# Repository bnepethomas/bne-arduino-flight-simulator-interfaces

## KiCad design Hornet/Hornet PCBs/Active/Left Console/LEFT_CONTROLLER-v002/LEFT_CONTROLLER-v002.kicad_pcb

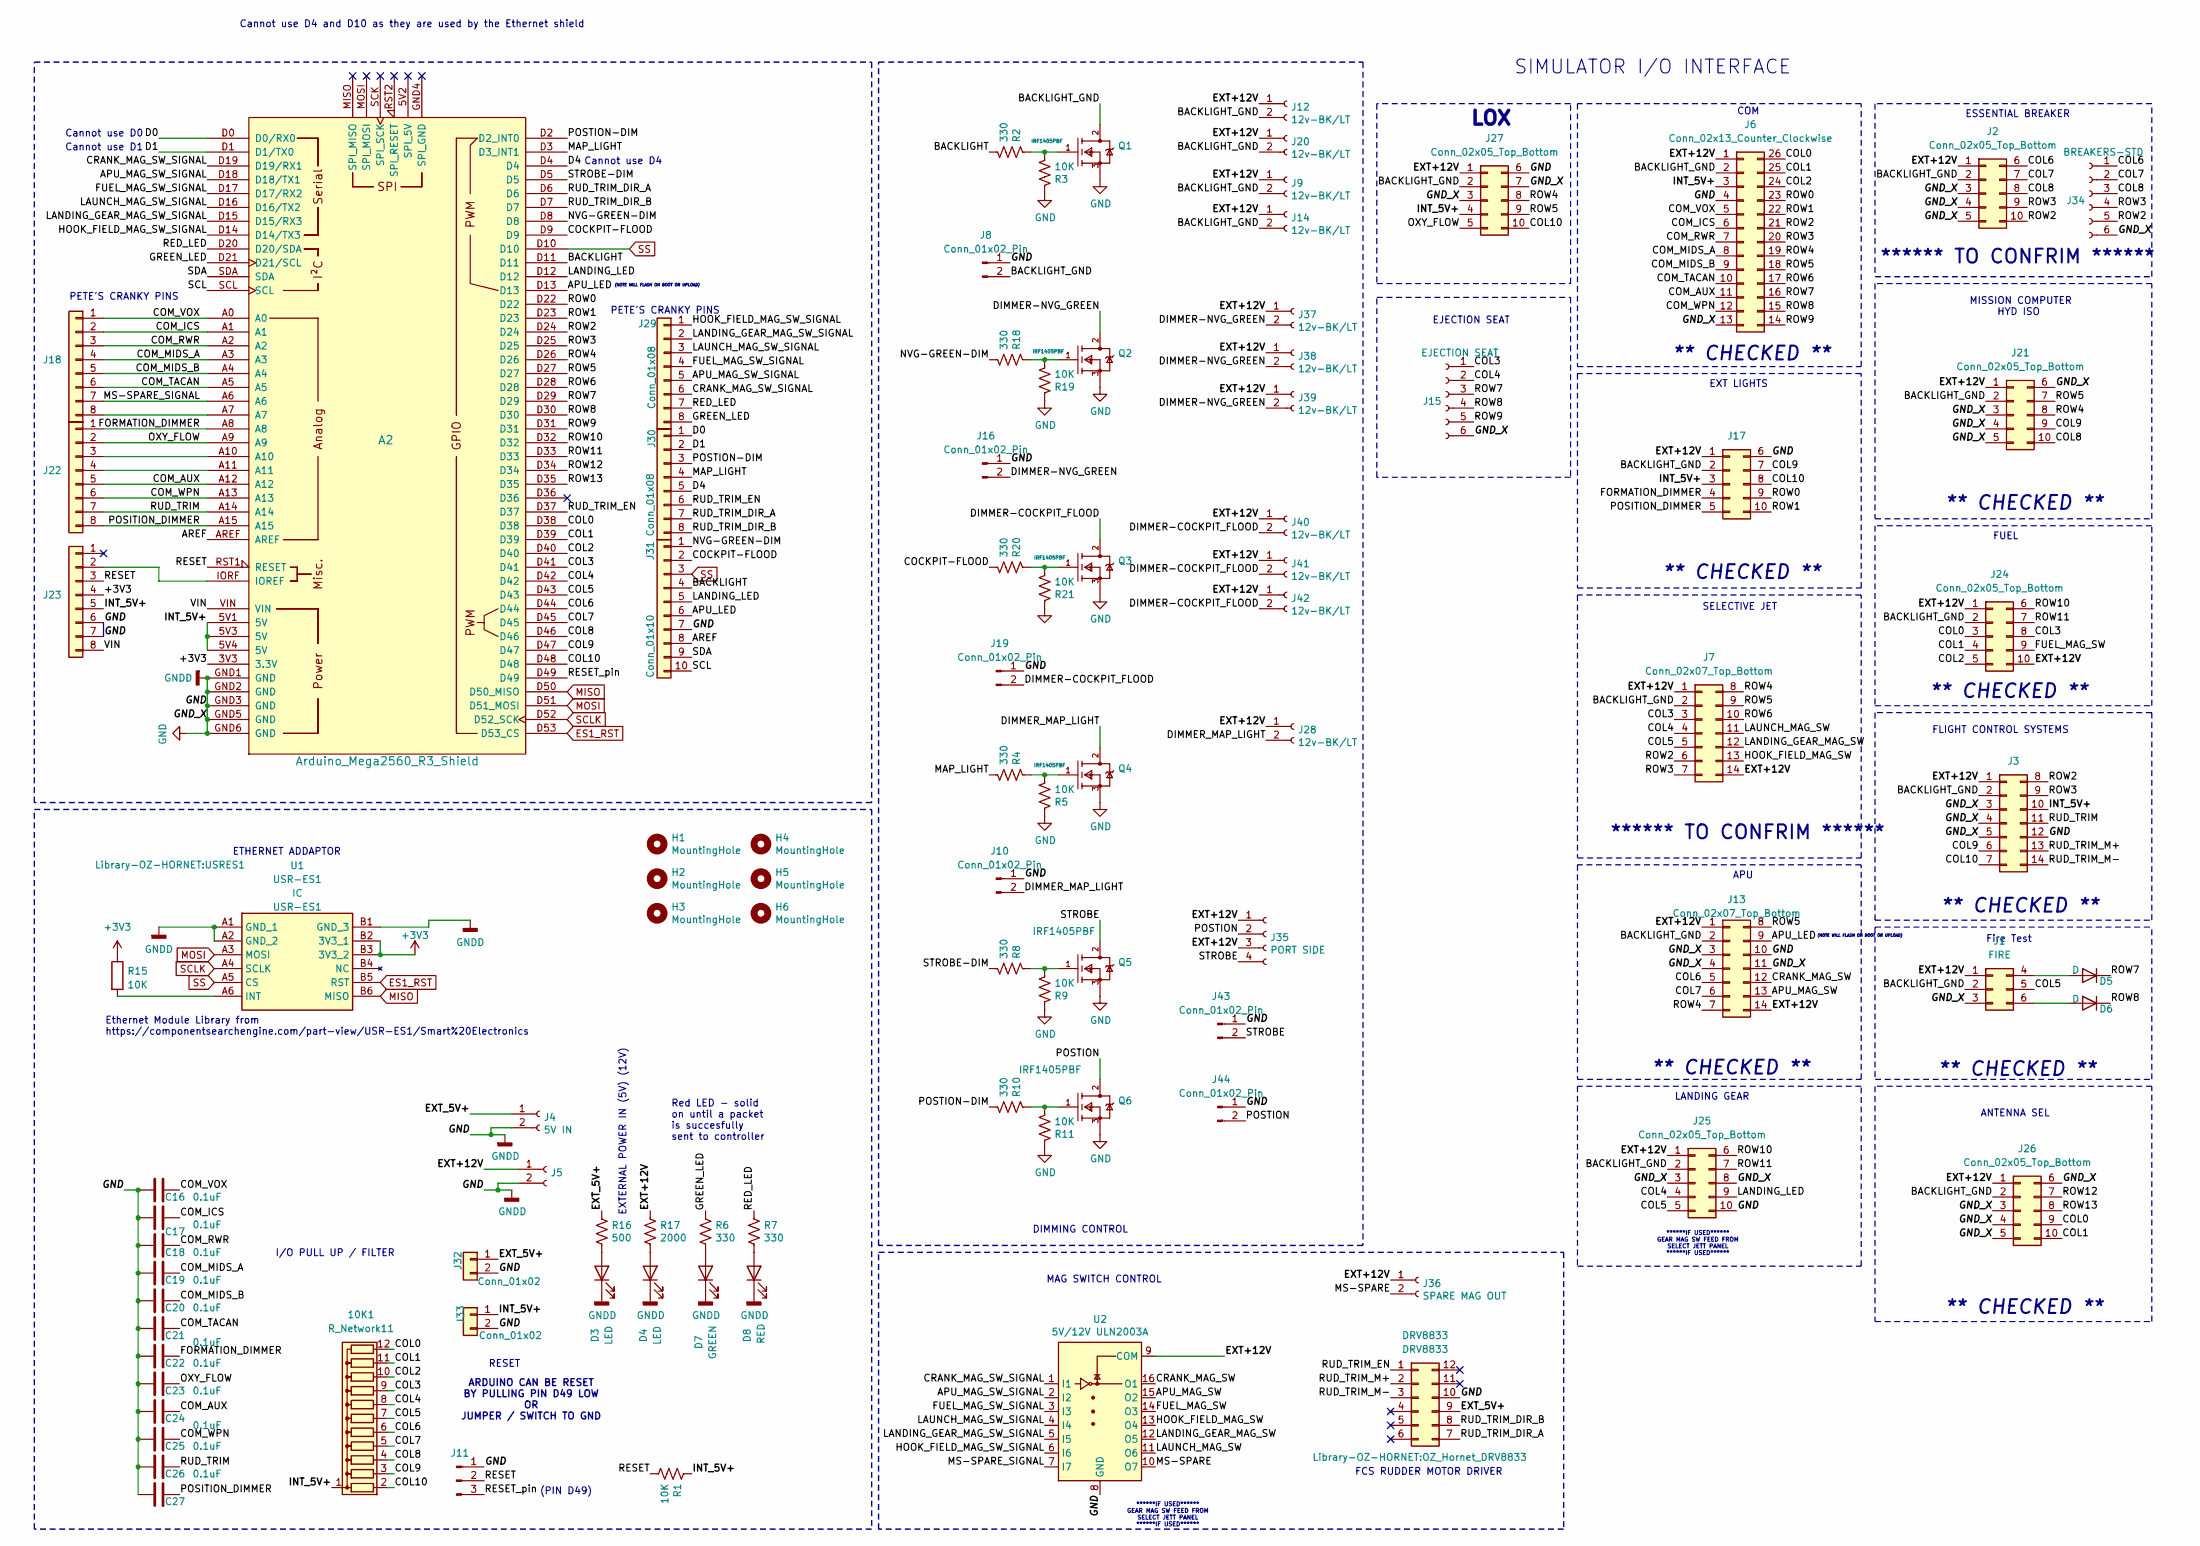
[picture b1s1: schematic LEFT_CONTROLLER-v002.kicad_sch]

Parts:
10K1: R_Network11; R_Array_SIP12
A2: Arduino_Mega2560_R3_Shield
C16, C17, C18, C19, C20, C21, C22, C23, C24, C25, C26, C27: 0.1uF; C_Disc_D4.3mm_W1.9mm_P5.00mm
D3, D4: LED; LED_D3.0mm
D5, D6: D; D_A-405_P7.62mm_Horizontal-SIGNAL
D7: GREEN; LED_D3.0mm
D8: RED; LED_D3.0mm
DRV8833: DRV8833; OZ_Hornet_DRV8833
H1, H2, H3, H4, H5, H6: MountingHole; MountingHole_3.2mm_M3
J1: FIRE; IDC-Header_2x03_P2.54mm_Vertical
J2, J17, J21, J24, J25, J26, J27: Conn_02x05_Top_Bottom; IDC-Header_2x05_P2.54mm_Vertical
J3, J7, J13: Conn_02x07_Top_Bottom; IDC-Header_2x07_P2.54mm_Vertical
J4: 5V IN; BarrelJack_Horizontal
J5: STEPPER IN 12-20VDC; BarrelJack_Horizontal
J6: Conn_02x13_Counter_Clockwise; IDC-Header_2x13_P2.54mm_Vertical
J8, J10, J16, J19, J43, J44: Conn_01x02_Pin; PinHeader_1x02_P2.54mm_Vertical
J9, J12, J14, J20, J28, J37, J38, J39, J40, J41, J42: 12v-BK/LT; Molex_KK-254_AE-6410-02A_1x02_P2.54mm_Vertical
J11: Conn_01x03_Pin; PinHeader_1x03_P2.54mm_Vertical
J15: EJECTION SEAT; Molex_KK-254_AE-6410-06A_1x06_P2.54mm_Vertical
J18, J22, J23, J29, J30: Conn_01x08; PinHeader_1x08_P2.54mm_Vertical
J31: Conn_01x10; PinHeader_1x10_P2.54mm_Vertical
J32, J33: Conn_01x02; PinHeader_1x02_P2.54mm_Vertical
J34: BREAKERS-STD; Molex_KK-254_AE-6410-06A_1x06_P2.54mm_Vertical
J35: PORT SIDE; Molex_KK-254_AE-6410-04A_1x04_P2.54mm_Vertical
J36: SPARE MAG OUT; Molex_KK-254_AE-6410-02A_1x02_P2.54mm_Vertical
Q1, Q2, Q3, Q4, Q5, Q6: IRF1405PBF; TO-220-3_Vertical; mouser part number 942-IRF1405PBF; digikey description MOSFET N-CH 55V 169A TO-220AB
R1, R3, R5, R9, R11, R15, R19, R21: 10K; R_Axial_DIN0204_L3.6mm_D1.6mm_P7.62mm_Horizontal
R2, R4, R6, R7, R8, R10, R18, R20: 330; R_Axial_DIN0204_L3.6mm_D1.6mm_P7.62mm_Horizontal
R16: 500; R_Axial_DIN0204_L3.6mm_D1.6mm_P7.62mm_Horizontal
R17: 2000; R_Axial_DIN0204_L3.6mm_D1.6mm_P7.62mm_Horizontal
U1: USR-ES1; USRES1; Manufacturer_Part_Number USR-ES1
U2: 5V/12V ULN2003A; DIP-16_W7.62mm

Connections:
+3V3: A2.3V3 (3.3V), J23.4, R15.1, U1.B2 (3V3_1), U1.B3 (3V3_2)
/APU_LED: A2.D13, J13.9, J31.6
/APU_MAG_SW: J13.13, U2.15 (O2)
/APU_MAG_SW_SIGNAL: A2.D18 (D18/TX1), J29.5, U2.2 (I2)
/AREF: A2.AREF, J31.8
/BACKLIGHT: A2.D11, J31.4, R2.2
/BACKLIGHT_GND: J1.2, J2.2, J3.2, J6.2, J7.2, J8.2, J9.2, J12.2, J13.2, J14.2, J17.2, J20.2, J21.2, J24.2, J25.2, J26.2, J27.2, Q1.2 (D)
/COCKPIT-FLOOD: A2.D9, J31.2, R20.2
/COL0: 10K1.12 (R11), A2.D38, J6.26, J24.3, J26.9
/COL1: 10K1.11 (R10), A2.D39, J6.25, J24.4, J26.10
/COL2: 10K1.10 (R9), A2.D40, J6.24, J24.5
/COL3: 10K1.9 (R8), A2.D41, J7.3, J15.1, J24.8
/COL4: 10K1.8 (R7), A2.D42, J7.4, J15.2, J25.4
/COL5: 10K1.7 (R6), A2.D43, J1.5, J7.5, J25.5
/COL6: 10K1.6 (R5), A2.D44, J2.6, J13.5, J34.1
/COL7: 10K1.5 (R4), A2.D45, J2.7, J13.6, J34.2
/COL8: 10K1.4 (R3), A2.D46, J2.8, J21.10, J34.3
/COL9: 10K1.3 (R2), A2.D47, J3.6, J17.7, J21.9
/COL10: 10K1.2 (R1), A2.D48, J3.7, J17.8, J27.10
/COM_AUX: A2.A12, C24.1, J6.11, J22.5
/COM_ICS: A2.A1, C17.1, J6.6, J18.2
/COM_MIDS_A: A2.A3, C19.1, J6.8, J18.4
/COM_MIDS_B: A2.A4, C20.1, J6.9, J18.5
/COM_RWR: A2.A2, C18.1, J6.7, J18.3
/COM_TACAN: A2.A5, C21.1, J6.10, J18.6
/COM_VOX: A2.A0, C16.1, J6.5, J18.1
/COM_WPN: A2.A13, C25.1, J6.12, J22.6
/CRANK_MAG_SW: J13.12, U2.16 (O1)
/CRANK_MAG_SW_SIGNAL: A2.D19 (D19/RX1), J29.6, U2.1 (I1)
/D0: A2.D0 (D0/RX0), J30.1
/D1: A2.D1 (D1/TX0), J30.2
/D4: A2.D4, J30.5
/DIMMER-COCKPIT_FLOOD: J19.2, J40.2, J41.2, J42.2, Q3.2 (D)
/DIMMER-NVG_GREEN: J16.2, J37.2, J38.2, J39.2, Q2.2 (D)
/DIMMER_MAP_LIGHT: J10.2, J28.2, Q4.2 (D)
/EXT+12V: J1.1, J2.1, J3.1, J5.1, J6.1, J7.1, J7.14, J9.1, J12.1, J13.1, J13.14, J14.1, J17.1, J20.1, J21.1, J24.1, J24.10, J25.1, J26.1, J27.1, J28.1, J35.1, J35.3, J36.1, J37.1, J38.1, J39.1, J40.1, J41.1, J42.1, R17.1, U2.9 (COM)
/EXT_5V+: DRV8833.9, J4.1, J32.1, R16.1
/FORMATION_DIMMER: A2.A8, C22.1, J17.4, J22.1
/FUEL_MAG_SW: J24.9, U2.14 (O3)
/FUEL_MAG_SW_SIGNAL: A2.D17 (D17/RX2), J29.4, U2.3 (I3)
/GREEN_LED: A2.D21 (D21/SCL), J29.8, R6.1
/HOOK_FIELD_MAG_SW: J7.13, U2.13 (O4)
/HOOK_FIELD_MAG_SW_SIGNAL: A2.D14 (D14/TX3), J29.1, U2.6 (I6)
/INT_5V+: 10K1.1 (common), A2.5V1 (5V), A2.5V3 (5V), A2.5V4 (5V), J3.10, J6.3, J17.3, J23.5, J27.4, J33.1, R1.1
/LANDING_GEAR_MAG_SW: J7.12, U2.12 (O5)
/LANDING_GEAR_MAG_SW_SIGNAL: A2.D15 (D15/RX3), J29.2, U2.5 (I5)
/LANDING_LED: A2.D12, J25.9, J31.5
/LAUNCH_MAG_SW: J7.11, U2.11 (O6)
/LAUNCH_MAG_SW_SIGNAL: A2.D16 (D16/TX2), J29.3, U2.4 (I4)
/MAP_LIGHT: A2.D3 (D3_INT1), J30.4, R4.2
/MS-SPARE: J36.2, U2.10 (O7)
/MS-SPARE_SIGNAL: A2.A6, J18.7, U2.7 (I7)
/NVG-GREEN-DIM: A2.D8, J31.1, R18.2
/OXY_FLOW: A2.A9, C23.1, J22.2, J27.5
/POSITION_DIMMER: A2.A15, C27.1, J17.5, J22.8
/POSTION: J35.2, J44.2, Q6.2 (D)
/POSTION-DIM: A2.D2 (D2_INT0), J30.3, R10.2
/RED_LED: A2.D20 (D20/SDA), J29.7, R7.1
/RESET: A2.RST1 (RESET), J11.2, J23.3, R1.2
/RESET_pin: A2.D49, J11.3
/ROW0: A2.D22, J6.23, J17.9
/ROW1: A2.D23, J6.22, J17.10
/ROW2: A2.D24, J2.10, J3.8, J6.21, J7.6, J34.5
/ROW3: A2.D25, J2.9, J3.9, J6.20, J7.7, J34.4
/ROW4: A2.D26, J6.19, J7.8, J13.7, J21.8, J27.8
/ROW5: A2.D27, J6.18, J7.9, J13.8, J21.7, J27.9
/ROW6: A2.D28, J6.17, J7.10
/ROW7: A2.D29, D5.1 (K), J6.16, J15.3
/ROW8: A2.D30, D6.1 (K), J6.15, J15.4
/ROW9: A2.D31, J6.14, J15.5
/ROW10: A2.D32, J24.6, J25.6
/ROW11: A2.D33, J24.7, J25.7
/ROW12: A2.D34, J26.7
/ROW13: A2.D35, J26.8
/RUD_TRIM: A2.A14, C26.1, J3.11, J22.7
/RUD_TRIM_DIR_A: A2.D6, DRV8833.7, J30.7
/RUD_TRIM_DIR_B: A2.D7, DRV8833.8, J30.8
/RUD_TRIM_EN: A2.D37, DRV8833.1, J30.6
/RUD_TRIM_M+: DRV8833.2, J3.13
/RUD_TRIM_M-: DRV8833.3, J3.14
/SCL: A2.SCL, J31.10
/SDA: A2.SDA, J31.9
/STROBE: J35.4, J43.2, Q5.2 (D)
/STROBE-DIM: A2.D5, R8.2
/VIN: A2.VIN, J23.8
ES1_RST: A2.D53 (D53_CS), U1.B5 (RST)
GND: A2.GND1 (GND), A2.GND2 (GND), A2.GND3 (GND), A2.GND5 (GND), A2.GND6 (GND), C16.2, C17.2, C18.2, C19.2, C20.2, C21.2, C22.2, C23.2, C24.2, C25.2, C26.2, C27.2, D3.1 (K), D4.1 (K), D7.1 (K), D8.1 (K), DRV8833.10, J1.3, J2.3, J2.4, J2.5, J3.3, J3.4, J3.5, J3.12, J4.2, J5.2, J6.4, J6.13, J8.1, J10.1, J11.1, J13.3, J13.4, J13.10, J13.11, J15.6, J16.1, J17.6, J19.1, J21.3, J21.4, J21.5, J21.6, J23.6, J23.7, J25.3, J25.8, J25.10, J26.3, J26.4, J26.5, J26.6, J27.3, J27.6, J27.7, J31.7, J32.2, J33.2, J34.6, J43.1, J44.1, Q1.3 (S), Q2.3 (S), Q3.3 (S), Q4.3 (S), Q5.3 (S), Q6.3 (S), R3.1, R5.1, R9.1, R11.1, R19.1, R21.1, U1.A1 (GND_1), U1.A2 (GND_2), U1.B1 (GND_3), U2.8 (GND)
MISO: A2.D50 (D50_MISO), U1.B6 (MISO)
MOSI: A2.D51 (D51_MOSI), U1.A3 (MOSI)
unnamed: A2.IORF (IOREF), J23.2
unnamed: D3.2 (A), R16.2
unnamed: D4.2 (A), R17.2
unnamed: D5.2 (A), J1.4
unnamed: D6.2 (A), J1.6
unnamed: D7.2 (A), R6.2
unnamed: D8.2 (A), R7.2
unnamed: A2.A7, J18.8
unnamed: A2.A10, J22.3
unnamed: A2.A11, J22.4
unnamed: Q1.1 (G), R2.1, R3.2
unnamed: Q2.1 (G), R18.1, R19.2
unnamed: Q3.1 (G), R20.1, R21.2
unnamed: Q4.1 (G), R4.1, R5.2
unnamed: Q5.1 (G), R8.1, R9.2
unnamed: Q6.1 (G), R10.1, R11.2
unnamed: R15.2, U1.A6 (INT)
SCLK: A2.D52 (D52_SCK), U1.A4 (SCLK)
SS: A2.D10, J31.3, U1.A5 (CS)

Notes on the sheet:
ANTENNA SEL
** CHECKED **
(NOTE WILL FLASH ON BOOT OR UPLOAD)
EJECTION SEAT
EXT LIGHTS
COM
Fire Test
FLIGHT CONTROL SYSTEMS
PETE'S CRANKY PINS
******IF USED****** GEAR MAG SW FEED FROM SELECT JETT PANEL ******IF USED******
SIMULATOR I/O INTERFACE
EXTERNAL POWER IN (5V) (12V)
RESET
****** TO CONFRIM ******
FUEL
APU
I/O PULL UP / FILTER
Cannot use D1
Cannot use D0
ESSENTIAL BREAKER
FCS RUDDER MOTOR DRIVER
LOX
HYD ISO
DIMMING CONTROL
ARDUINO CAN BE RESET BY PULLING PIN D49 LOW OR JUMPER / SWITCH TO GND
ETHERNET ADDAPTOR
SELECTIVE JET
Cannot use D4
Ethernet Module Library from https://componentsearchengine.com/part-view/USR-ES1/Smart%20Electronics
Red LED - solid on until a packet is succesfully sent to controller
(PIN D49)
MAG SWITCH CONTROL
Cannot use D4 and D10 as they are used by the Ethernet shield
LANDING GEAR
MISSION COMPUTER

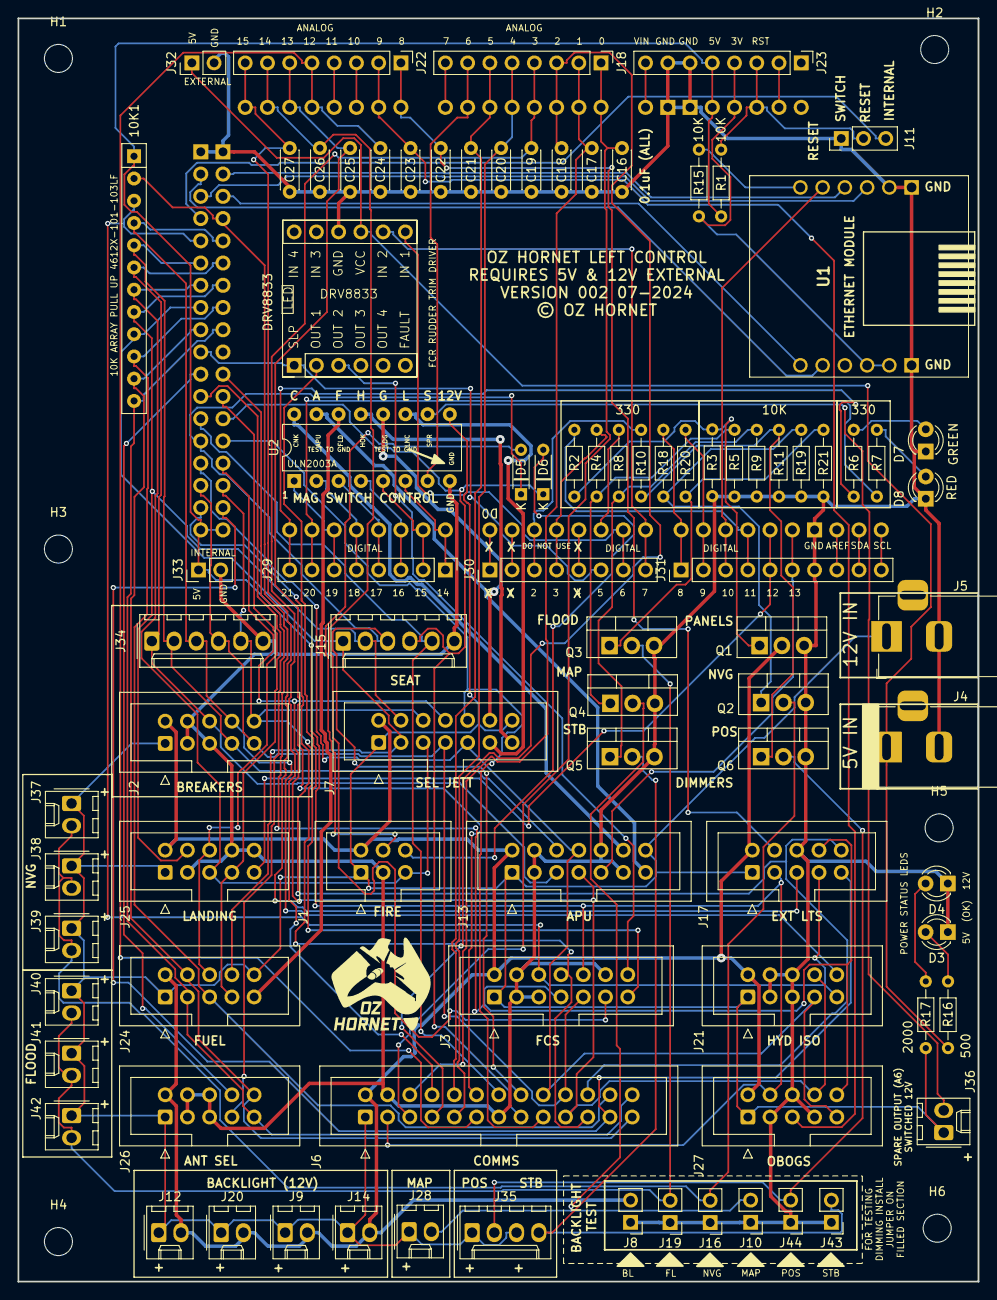
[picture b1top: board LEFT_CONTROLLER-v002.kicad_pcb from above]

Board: 2 copper layers, 109.7 x 144.3 mm, 97 parts (0 on the bottom side), 108 nets.

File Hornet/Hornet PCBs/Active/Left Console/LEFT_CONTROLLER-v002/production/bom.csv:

Designator,Footprint,Quantity,Value,LCSC Part #
10K1,R_Array_SIP12,1,R_Network11,
A2,Arduino_Mega2560_R3_Shield,1,Arduino_Mega2560_R3_Shield,
"C16, C17, C18, C19, C20, C21, C22, C23, C24, C25, C26, C27",C_Disc_D4.3mm_W1.9mm_P5.00mm,12,0.1uF,
"D3, D4",LED_D3.0mm,2,LED,
"D5, D6",D_A-405_P7.62mm_Horizontal-SIGNAL,2,D,
D7,LED_D3.0mm,1,GREEN,
D8,LED_D3.0mm,1,RED,
DRV8833,OZ_Hornet_DRV8833,1,DRV8833,
"H1, H2, H3, H4, H5, H6",MountingHole_3.2mm_M3,6,MountingHole,
J1,IDC-Header_2x03_P2.54mm_Vertical,1,FIRE,
"J10, J16, J19, J43, J44, J8",PinHeader_1x02_P2.54mm_Vertical,6,Conn_01x02_Pin,
J11,PinHeader_1x03_P2.54mm_Vertical,1,Conn_01x03_Pin,
"J12, J14, J20, J28, J37, J38, J39, J40, J41, J42, J9",Molex_KK-254_AE-6410-02A_1x02_P2.54mm_Vertical,11,12v-BK/LT,
"J13, J3, J7",IDC-Header_2x07_P2.54mm_Vertical,3,Conn_02x07_Top_Bottom,
J15,Molex_KK-254_AE-6410-06A_1x06_P2.54mm_Vertical,1,EJECTION SEAT,
"J17, J2, J21, J24, J25, J26, J27",IDC-Header_2x05_P2.54mm_Vertical,7,Conn_02x05_Top_Bottom,
"J18, J22, J23, J29, J30",PinHeader_1x08_P2.54mm_Vertical,5,Conn_01x08,
J31,PinHeader_1x10_P2.54mm_Vertical,1,Conn_01x10,
"J32, J33",PinHeader_1x02_P2.54mm_Vertical,2,Conn_01x02,
J34,Molex_KK-254_AE-6410-06A_1x06_P2.54mm_Vertical,1,BREAKERS-STD,
J35,Molex_KK-254_AE-6410-04A_1x04_P2.54mm_Vertical,1,PORT SIDE,
J36,Molex_KK-254_AE-6410-02A_1x02_P2.54mm_Vertical,1,SPARE MAG OUT,
J4,BarrelJack_Horizontal,1,5V IN,
J5,BarrelJack_Horizontal,1,STEPPER IN 12-20VDC,
J6,IDC-Header_2x13_P2.54mm_Vertical,1,Conn_02x13_Counter_Clockwise,
"Q1, Q2, Q3, Q4, Q5, Q6",TO-220-3_Vertical,6,IRF1405PBF,
"R1, R11, R15, R19, R21, R3, R5, R9",R_Axial_DIN0204_L3.6mm_D1.6mm_P7.62mm_Horizontal,8,10K,
"R10, R18, R2, R20, R4, R6, R7, R8",R_Axial_DIN0204_L3.6mm_D1.6mm_P7.62mm_Horizontal,8,330,
R16,R_Axial_DIN0204_L3.6mm_D1.6mm_P7.62mm_Horizontal,1,500,
R17,R_Axial_DIN0204_L3.6mm_D1.6mm_P7.62mm_Horizontal,1,2000,
U1,USRES1,1,USR-ES1,
U2,DIP-16_W7.62mm,1,5V/12V ULN2003A,

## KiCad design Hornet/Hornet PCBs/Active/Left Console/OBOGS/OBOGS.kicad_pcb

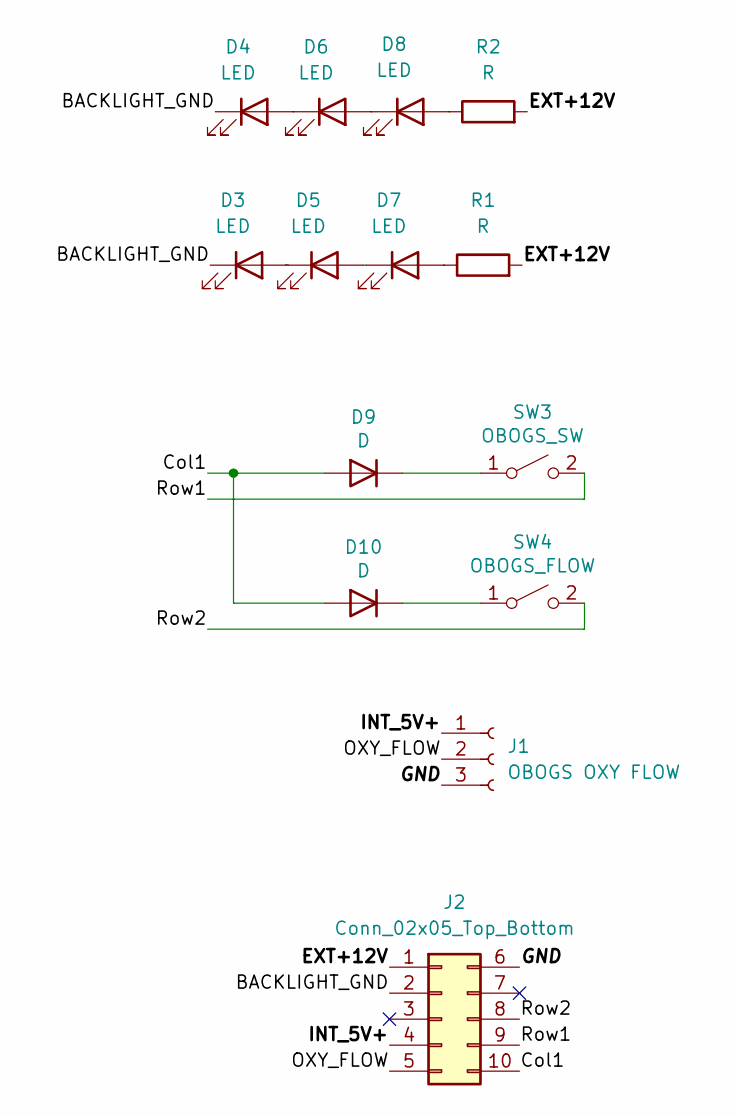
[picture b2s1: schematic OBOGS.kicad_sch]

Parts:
D3, D4, D5, D6, D7, D8: LED; LED_D3.0mm_FlatTop
D9, D10: D; D_A-405_P7.62mm_Horizontal-SIGNAL
J1: OBOGS OXY FLOW; JST_XH_B3B-XH-A_1x03_P2.50mm_Vertical
J2: Conn_02x05_Top_Bottom; IDC-Header_2x05_P2.54mm_Vertical
R1, R2: R; R_Axial_DIN0204_L3.6mm_D1.6mm_P7.62mm_Horizontal
SW3: OBOGS_SW; JST_XH_B2B-XH-A_1x02_P2.50mm_Vertical
SW4: OBOGS_FLOW; JST_XH_B2B-XH-A_1x02_P2.50mm_Vertical

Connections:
/BACKLIGHT_GND: D3.1 (K), D4.1 (K), J2.2
/Col1: D9.2 (A), D10.2 (A), J2.10
/EXT+12V: J2.1, R1.2, R2.2
/GND: J1.3, J2.6
/INT_5V+: J1.1, J2.4
/OXY_FLOW: J1.2, J2.5
/Row1: J2.9, SW3.2 (B)
/Row2: J2.8, SW4.2 (B)
unnamed: D3.2 (A), D5.1 (K)
unnamed: D4.2 (A), D6.1 (K)
unnamed: D5.2 (A), D7.1 (K)
unnamed: D6.2 (A), D8.1 (K)
unnamed: D7.2 (A), R1.1
unnamed: D8.2 (A), R2.1
unnamed: D9.1 (K), SW3.1 (A)
unnamed: D10.1 (K), SW4.1 (A)

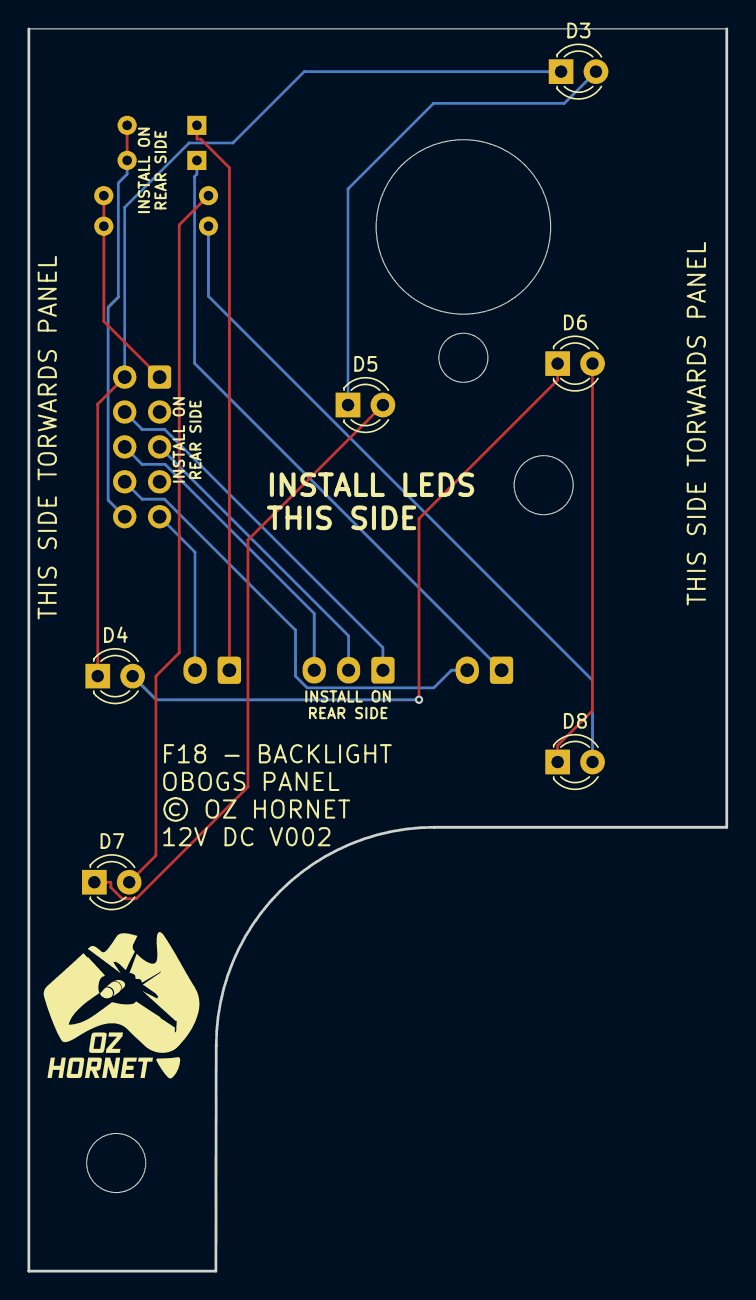
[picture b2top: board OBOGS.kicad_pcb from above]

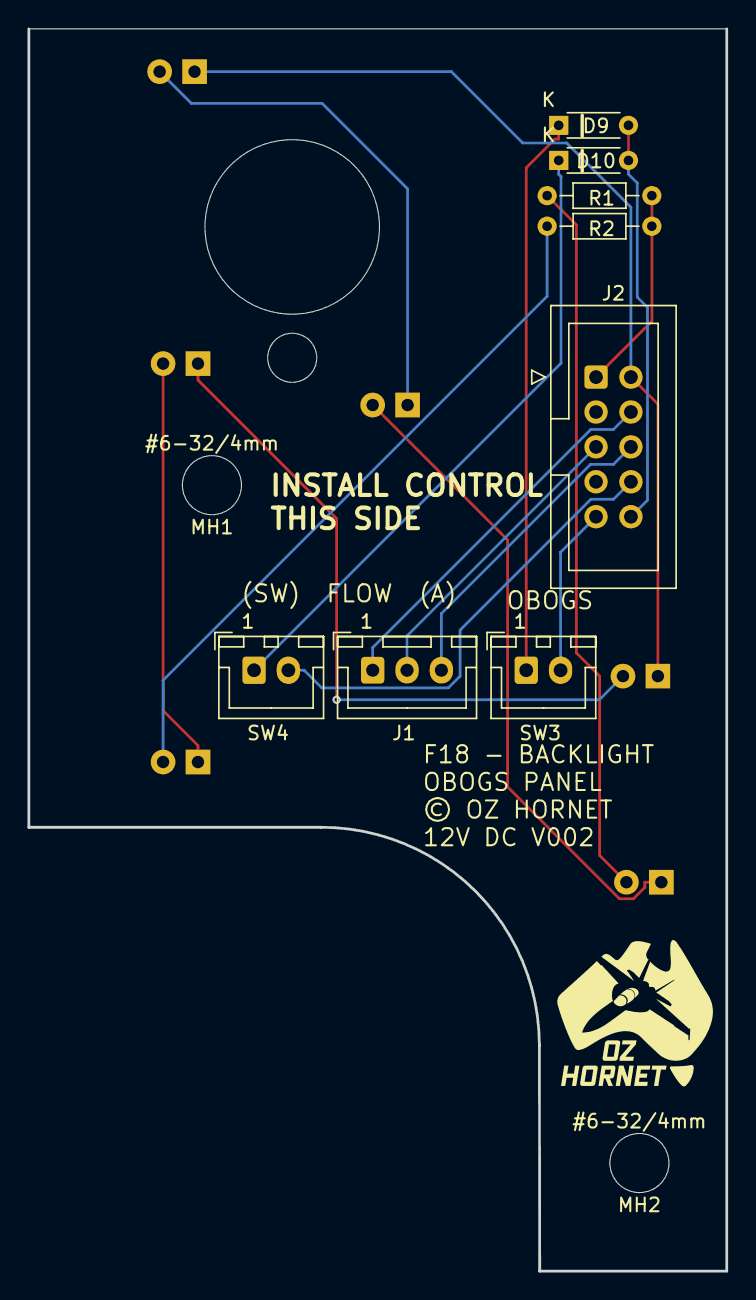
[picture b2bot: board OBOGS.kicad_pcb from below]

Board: 2 copper layers, 50.8 x 90.4 mm, 17 parts (10 on the bottom side), 16 nets.

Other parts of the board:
MH1, MH2: 6x32 / 4mm; MountingHole_6-32_PHS
MH3: Switch_100SPx; 100SPX_Toggle_13mm_x_18mm

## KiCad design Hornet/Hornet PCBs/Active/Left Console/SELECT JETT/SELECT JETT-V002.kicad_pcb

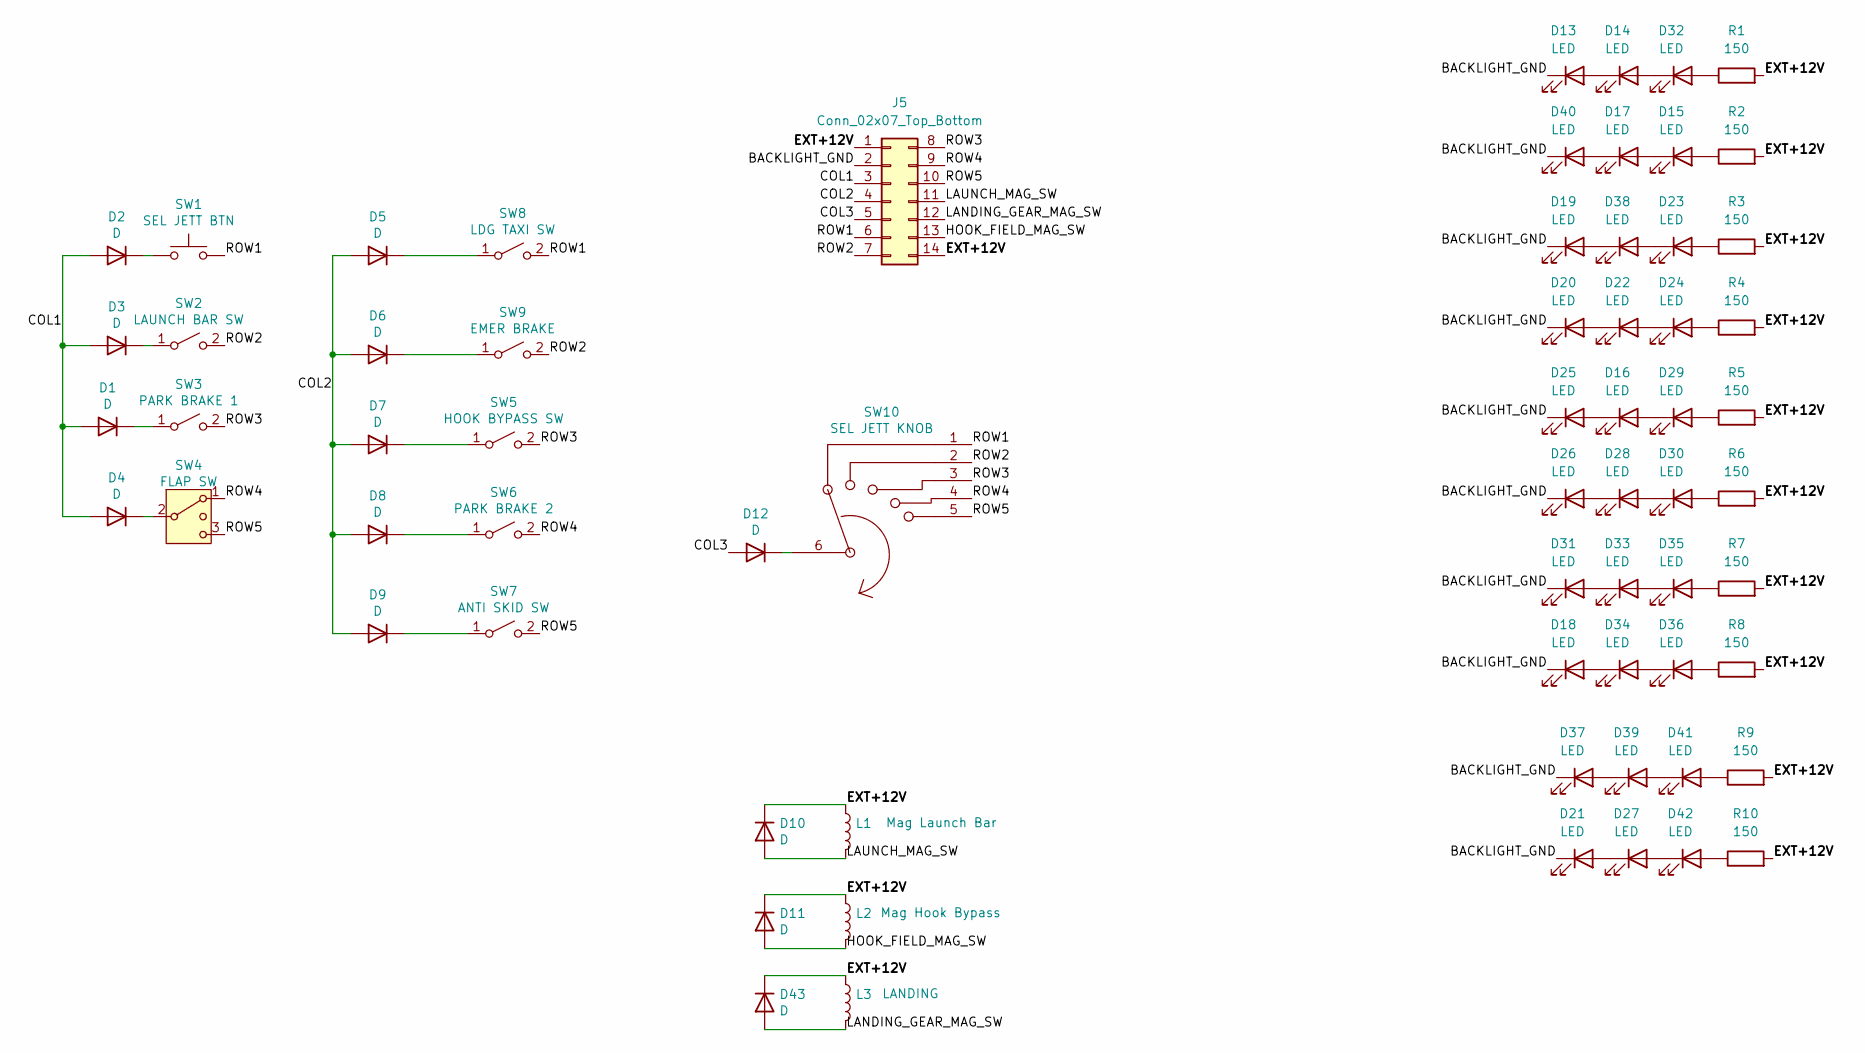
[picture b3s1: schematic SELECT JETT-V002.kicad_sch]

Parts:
D1, D2, D3, D4, D5, D6, D7, D8, D9, D12: D; D_A-405_P7.62mm_Horizontal-SIGNAL
D10, D11, D43: D; D_DO-41_SOD81_P10.16mm_Horizontal
D13, D14, D15, D16, D17, D18, D19, D20, D21, D22, D23, D24, D25, D26, D27, D28, D29, D30, D31, D32, D33, D34, D35, D36, D37, D38, D39, D40, D41, D42: LED; LED_D3.0mm_FlatTop
J5: Conn_02x07_Top_Bottom; IDC-Header_2x07_P2.54mm_Vertical
L1: Mag Launch Bar; JST_XH_B2B-XH-A_1x02_P2.50mm_Vertical
L2: Mag Hook Bypass; JST_XH_B2B-XH-A_1x02_P2.50mm_Vertical
L3: LANDING; JST_XH_B2B-XH-A_1x02_P2.50mm_Vertical
R1, R2, R3, R4, R5, R6, R7, R8, R9, R10: 150; R_Axial_DIN0204_L3.6mm_D1.6mm_P7.62mm_Horizontal
SW1: SEL JETT BTN; JST_XH_B2B-XH-A_1x02_P2.50mm_Vertical
SW2: LAUNCH BAR SW; JST_XH_B2B-XH-A_1x02_P2.50mm_Vertical
SW3: PARK BRAKE 1; JST_XH_B2B-XH-A_1x02_P2.50mm_Vertical
SW4: FLAP SW; JST_XH_B3B-XH-A_1x03_P2.50mm_Vertical
SW5: HOOK BYPASS SW; JST_XH_B2B-XH-A_1x02_P2.50mm_Vertical
SW6: PARK BRAKE 2; JST_XH_B2B-XH-A_1x02_P2.50mm_Vertical
SW7: ANTI SKID SW; JST_XH_B2B-XH-A_1x02_P2.50mm_Vertical
SW8: LDG TAXI SW; JST_XH_B2B-XH-A_1x02_P2.50mm_Vertical
SW9: EMER BRAKE; JST_XH_B2B-XH-A_1x02_P2.50mm_Vertical
SW10: SEL JETT KNOB; JST_XH_B6B-XH-A_1x06_P2.50mm_Vertical

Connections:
/BACKLIGHT_GND: D13.1 (K), D18.1 (K), D19.1 (K), D20.1 (K), D21.1 (K), D25.1 (K), D26.1 (K), D31.1 (K), D37.1 (K), D40.1 (K), J5.2
/COL1: D1.2 (A), D2.2 (A), D3.2 (A), D4.2 (A), J5.3
/COL2: D5.2 (A), D6.2 (A), D7.2 (A), D8.2 (A), D9.2 (A), J5.4
/COL3: D12.2 (A), J5.5
/EXT+12V: D10.1 (K), D11.1 (K), D43.1 (K), J5.1, J5.14, L1.1, L2.1, L3.1, R1.2, R2.2, R3.2, R4.2, R5.2, R6.2, R7.2, R8.2, R9.2, R10.2
/HOOK_FIELD_MAG_SW: D11.2 (A), J5.13, L2.2
/LANDING_GEAR_MAG_SW: D43.2 (A), J5.12, L3.2
/LAUNCH_MAG_SW: D10.2 (A), J5.11, L1.2
/ROW1: J5.6, SW1.2, SW8.2 (B), SW10.1
/ROW2: J5.7, SW2.2 (B), SW9.2 (B), SW10.2
/ROW3: J5.8, SW3.2 (B), SW5.2 (B), SW10.3
/ROW4: J5.9, SW4.1, SW6.2 (B), SW10.4
/ROW5: J5.10, SW4.3 (4), SW7.2 (B), SW10.5
unnamed: D1.1 (K), SW3.1 (A)
unnamed: D2.1 (K), SW1.1
unnamed: D3.1 (K), SW2.1 (A)
unnamed: D4.1 (K), SW4.2 (3)
unnamed: D5.1 (K), SW8.1 (A)
unnamed: D6.1 (K), SW9.1 (A)
unnamed: D7.1 (K), SW5.1 (A)
unnamed: D8.1 (K), SW6.1 (A)
unnamed: D9.1 (K), SW7.1 (A)
unnamed: D12.1 (K), SW10.6
unnamed: D13.2 (A), D14.1 (K)
unnamed: D14.2 (A), D32.1 (K)
unnamed: D15.2 (A), R2.1
unnamed: D15.1 (K), D17.2 (A)
unnamed: D16.2 (A), D29.1 (K)
unnamed: D16.1 (K), D25.2 (A)
unnamed: D17.1 (K), D40.2 (A)
unnamed: D18.2 (A), D34.1 (K)
unnamed: D19.2 (A), D38.1 (K)
unnamed: D20.2 (A), D22.1 (K)
unnamed: D21.2 (A), D27.1 (K)
unnamed: D22.2 (A), D24.1 (K)
unnamed: D23.2 (A), R3.1
unnamed: D23.1 (K), D38.2 (A)
unnamed: D24.2 (A), R4.1
unnamed: D26.2 (A), D28.1 (K)
unnamed: D27.2 (A), D42.1 (K)
unnamed: D28.2 (A), D30.1 (K)
unnamed: D29.2 (A), R5.1
unnamed: D30.2 (A), R6.1
unnamed: D31.2 (A), D33.1 (K)
unnamed: D32.2 (A), R1.1
unnamed: D33.2 (A), D35.1 (K)
unnamed: D34.2 (A), D36.1 (K)
unnamed: D35.2 (A), R7.1
unnamed: D36.2 (A), R8.1
unnamed: D37.2 (A), D39.1 (K)
unnamed: D39.2 (A), D41.1 (K)
unnamed: D41.2 (A), R9.1
unnamed: D42.2 (A), R10.1

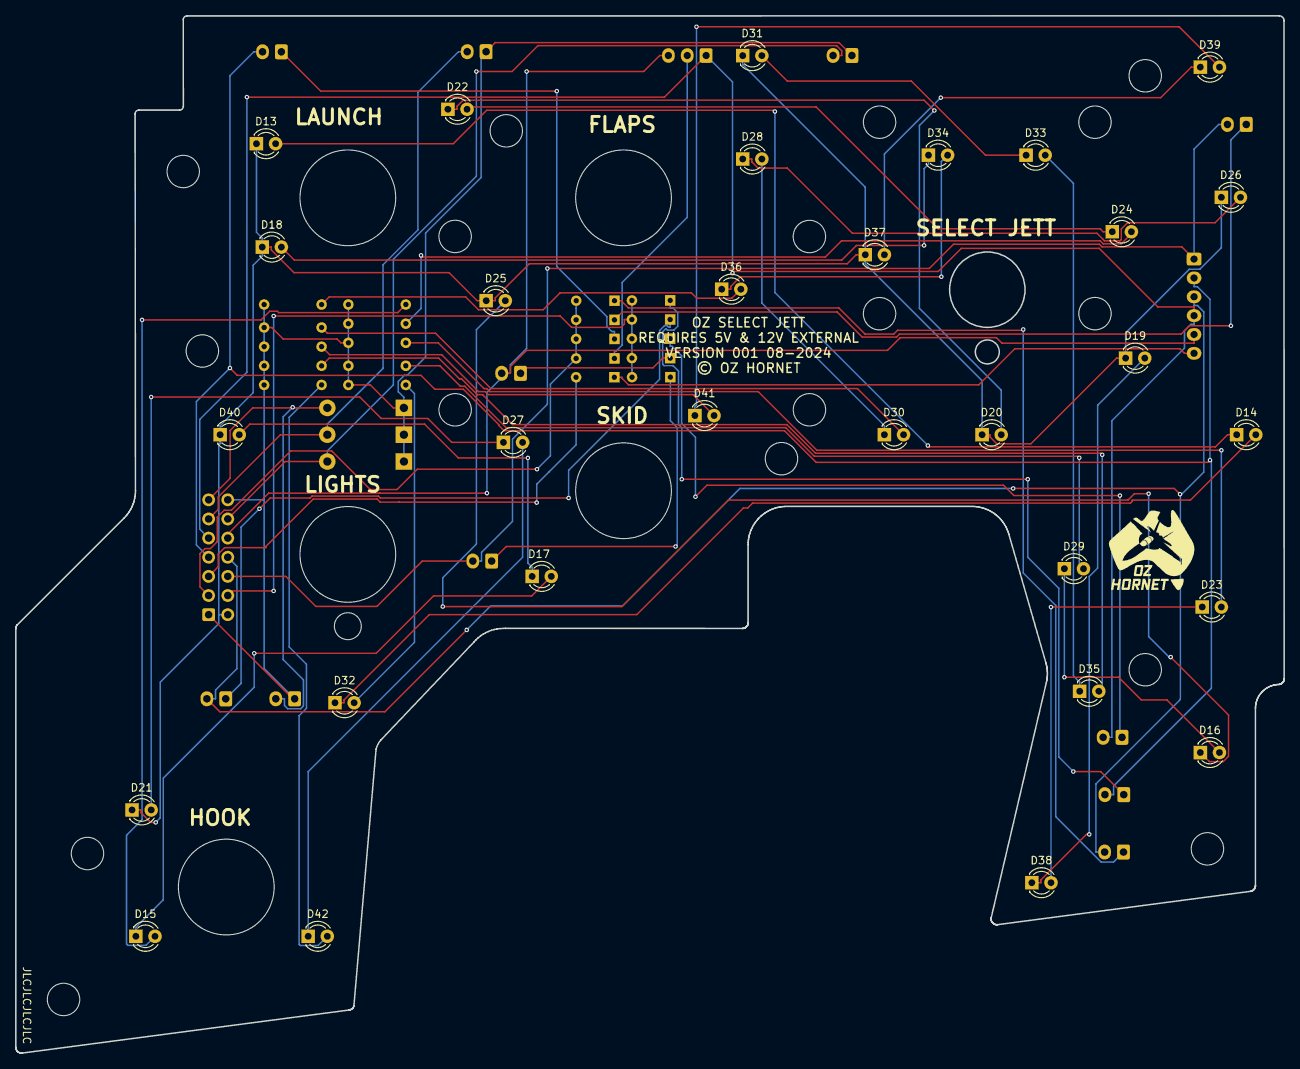
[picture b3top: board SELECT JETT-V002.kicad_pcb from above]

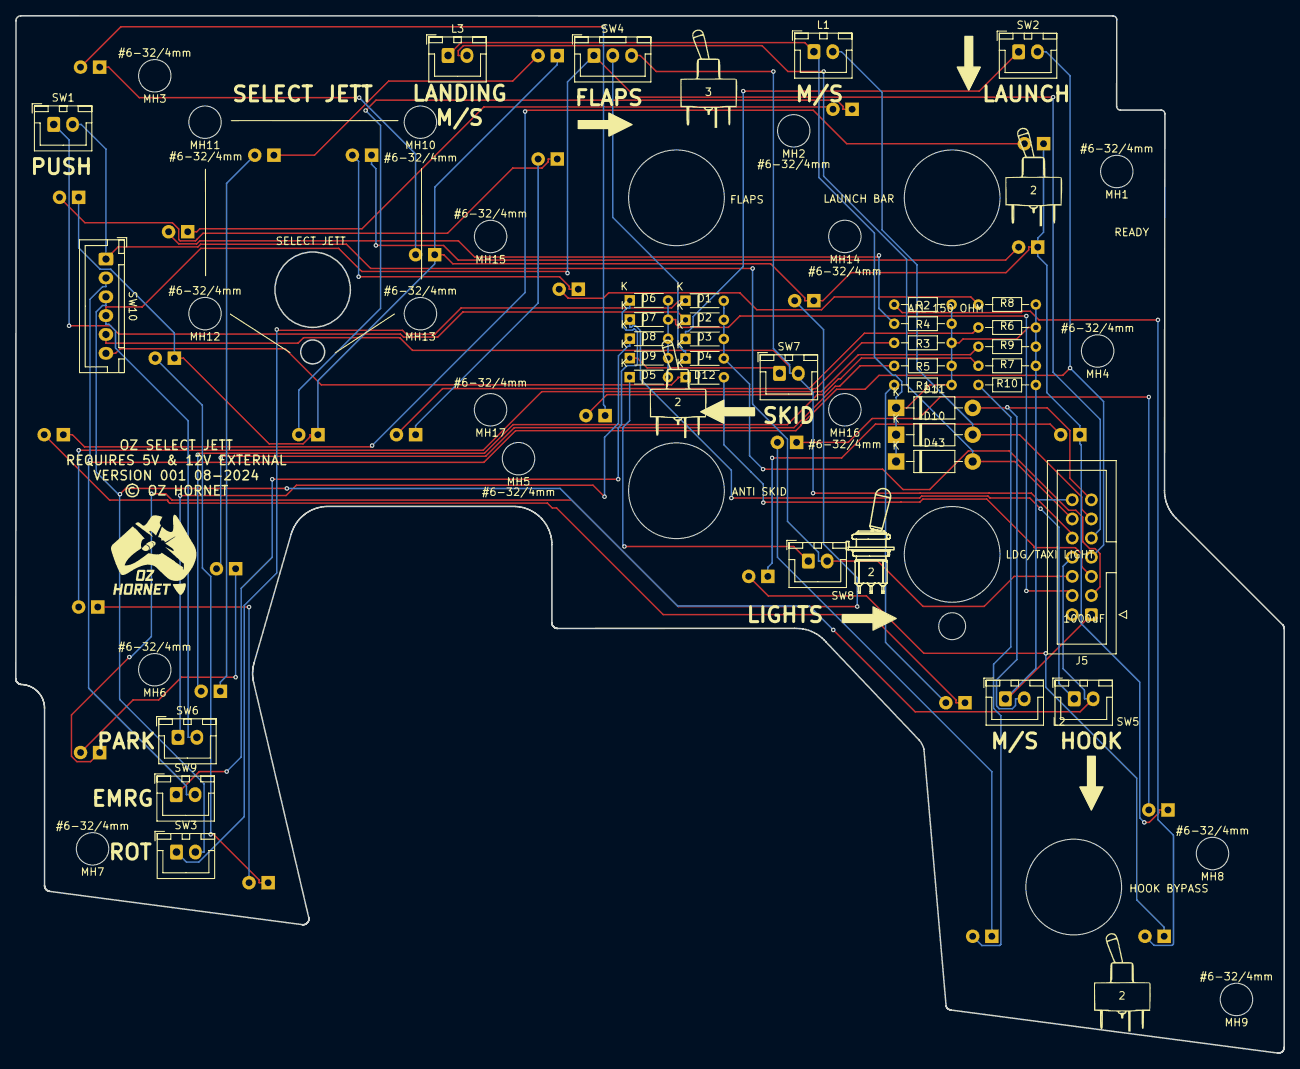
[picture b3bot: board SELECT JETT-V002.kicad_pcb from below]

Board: 2 copper layers, 168.3 x 137.6 mm, 94 parts (59 on the bottom side), 53 nets.

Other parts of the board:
LOGO3, LOGO5, LOGO6: LOGO; 631H2_Toggle_Silkscreen
LOGO4: LOGO; 631H3_Toggle_Silkscreen
LOGO7: LOGO; 100SP1_Toggle_Silkscreen
MH1, MH2, MH3, MH4, MH5, MH6, MH7, MH8, MH9, MH10, MH11, MH12, MH13, MH14, MH15, MH16, MH17: 6x32 / 4mm; MountingHole_6-32_PHS
MH22, MH23, MH24, MH25: Switch_631H; 631HX_Toggle_13mm_x_13mm
MH26: Switch_100SPx; 100SPX_Toggle_13mm_x_18mm

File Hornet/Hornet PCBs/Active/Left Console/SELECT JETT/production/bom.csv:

Designator,Footprint,Quantity,Value,LCSC Part #
"D1, D12, D2, D3, D4, D5, D6, D7, D8, D9",D_A-405_P7.62mm_Horizontal-SIGNAL,10,D,
"D10, D11, D43",D_DO-41_SOD81_P10.16mm_Horizontal,3,D,
"D13, D14, D15, D16, D17, D18, D19, D20, D21, D22, D23, D24, D25, D26, D27, D28, D29, D30, D31, D32, D33, D34, D35, D36, D37, D38, D39, D40, D41, D42",LED_D3.0mm_FlatTop,30,LED,
J5,IDC-Header_2x07_P2.54mm_Vertical,1,Conn_02x07_Top_Bottom,
L1,JST_XH_B2B-XH-A_1x02_P2.50mm_Vertical,1,Mag Launch Bar,
L2,JST_XH_B2B-XH-A_1x02_P2.50mm_Vertical,1,Mag Hook Bypass,
L3,JST_XH_B2B-XH-A_1x02_P2.50mm_Vertical,1,LANDING,
"R1, R10, R2, R3, R4, R5, R6, R7, R8, R9",R_Axial_DIN0204_L3.6mm_D1.6mm_P7.62mm_Horizontal,10,R,
SW1,JST_XH_B2B-XH-A_1x02_P2.50mm_Vertical,1,SEL JETT BTN,
SW10,JST_XH_B6B-XH-A_1x06_P2.50mm_Vertical,1,SEL JETT KNOB,
SW2,JST_XH_B2B-XH-A_1x02_P2.50mm_Vertical,1,LAUNCH BAR SW,
SW3,JST_XH_B2B-XH-A_1x02_P2.50mm_Vertical,1,PARK BRAKE 1,
SW4,JST_XH_B3B-XH-A_1x03_P2.50mm_Vertical,1,FLAP SW,
SW5,JST_XH_B2B-XH-A_1x02_P2.50mm_Vertical,1,HOOK BYPASS SW,
SW6,JST_XH_B2B-XH-A_1x02_P2.50mm_Vertical,1,PARK BRAKE 2,
SW7,JST_XH_B2B-XH-A_1x02_P2.50mm_Vertical,1,ANTI SKID SW,
SW8,JST_XH_B2B-XH-A_1x02_P2.50mm_Vertical,1,LDG TAXI SW,
SW9,JST_XH_B2B-XH-A_1x02_P2.50mm_Vertical,1,EMER BRAKE,

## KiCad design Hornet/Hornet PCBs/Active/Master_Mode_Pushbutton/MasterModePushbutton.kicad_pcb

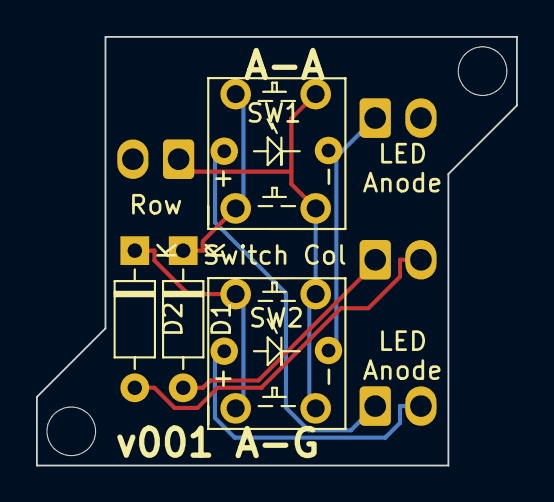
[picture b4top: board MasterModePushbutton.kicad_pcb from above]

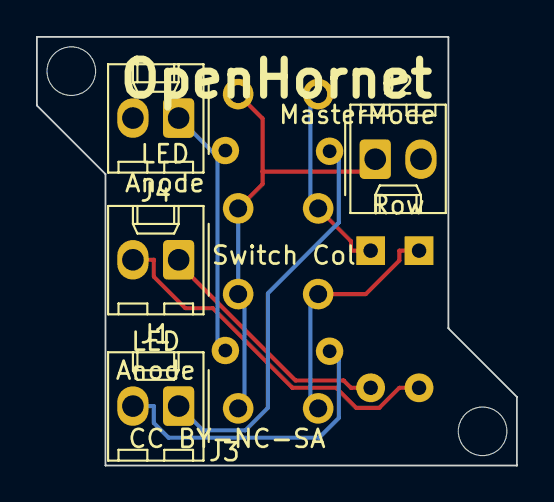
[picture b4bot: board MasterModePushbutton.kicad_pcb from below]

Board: 2 copper layers, 26.7 x 23.8 mm, 10 parts (4 on the bottom side), 8 nets.

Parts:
D1, D2: 1N4148; D_DO-35_SOD27_P7.62mm_Horizontal
H1, H2: Mouting_Hole_2.71mm; MountingHole_2.7mm_M2.5_ISO14580
J1, J2, J3, J4: Conn_01x02_Female; Molex_1x02_P2.54mm_Vertical
SW1, SW2: push; PT_Small_Tactile_Switch_With_LED

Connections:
unnamed: D1.1, SW1.1, SW1.2
unnamed: D1.2, J1.1
unnamed: D2.1, SW2.1, SW2.2
unnamed: D2.2, J1.2
unnamed: J2.1, SW1.3, SW1.4, SW2.3, SW2.4
unnamed: J3.1, SW1.5
unnamed: J3.2, SW2.5
unnamed: J4.1, SW1.6, SW2.6

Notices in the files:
Hornet/Hornet PCBs/Active/Left Console/LEFT_CONTROLLER-v002/LEFT_CONTROLLER-v002.kicad_pcb:
© OZ HORNET
Hornet/Hornet PCBs/Active/Master_Mode_Pushbutton/MasterModePushbutton.kicad_pcb:
CC BY-NC-SA
